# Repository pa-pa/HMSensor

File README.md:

# HMSensor

Flexible and tiny (40x20mm) Hardware Platform for 868MHz Sensors and Actors.

It comes in tow different variants:
* StepUp: For Batter or PowerSupply usage
* CR2032: For even smaller coin battery applications

Extensible with [AddOn-Boards](AddOns).

* Some (german) documentation is available at https://asksinpp.de/Projekte/psi/HMSensor
* Helper PCB for flashing: https://github.com/psi-4ward/HMSensor-FlashStation

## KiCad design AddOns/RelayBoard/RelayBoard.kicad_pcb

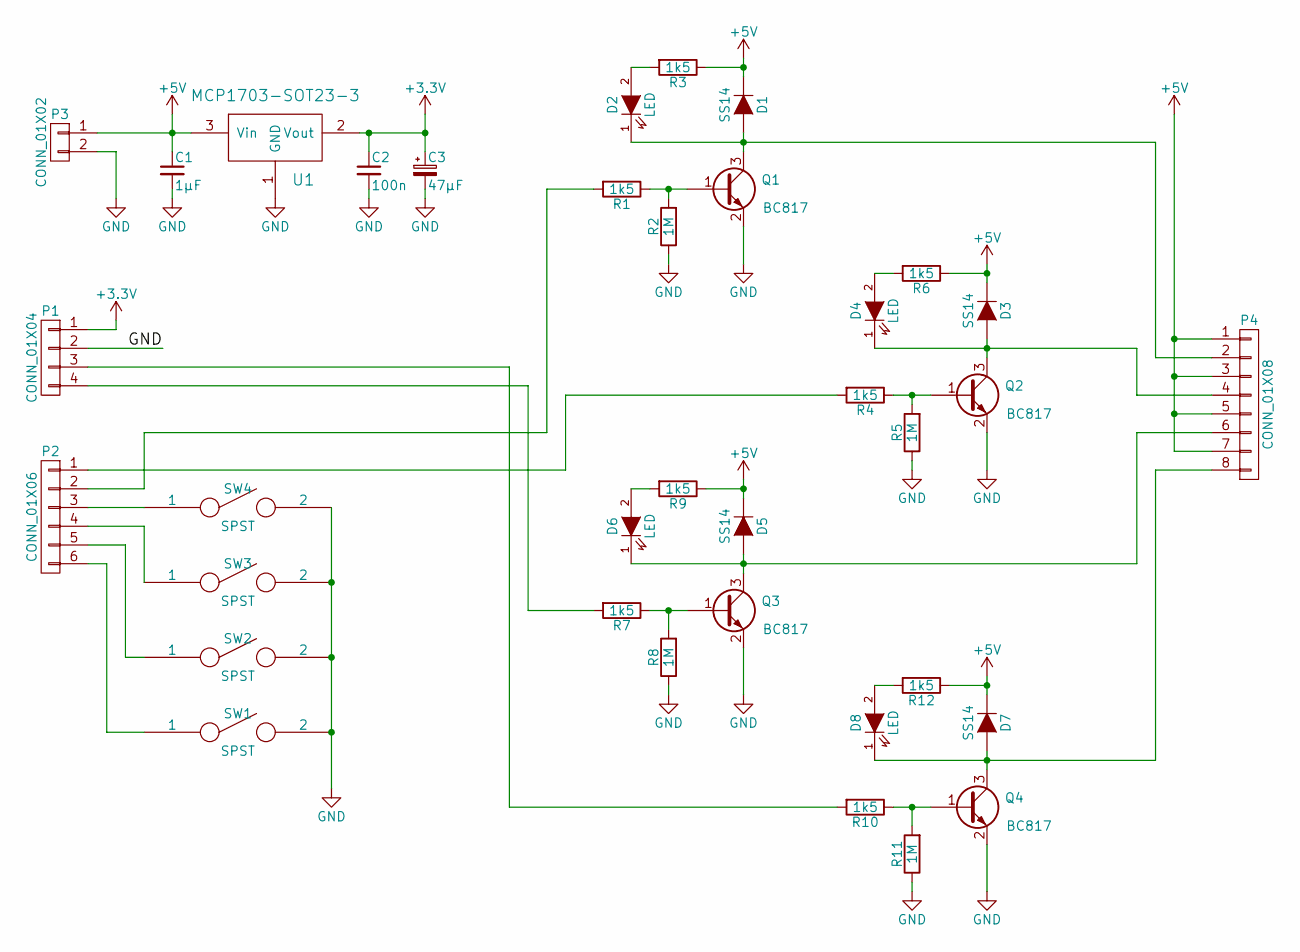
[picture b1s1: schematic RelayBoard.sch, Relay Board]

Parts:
C1: 1µF; C_0805
C2: 100n; C_0805
C3: 47µF; CP_Tantalum_Case-T_EIA-3528-12_Reflow
D1, D3, D5, D7: SS14; D_SMA
D2, D4, D6, D8: LED; LED_1206
P1: CONN_01X04; Pin_Header_Straight_1x04_Pitch2.54mm
P2: CONN_01X06; Pin_Header_Straight_1x06_Pitch2.54mm
P3: CONN_01X02; Pin_Header_Straight_1x02_Pitch2.54mm
P4: CONN_01X08; Pin_Header_Straight_1x08_Pitch2.54mm
Q1, Q2, Q3, Q4: BC817; SOT-23-3
R1, R3, R4, R6, R7, R9, R10, R12: 1k5; R_0805
R2, R5, R8, R11: 1M; R_0805
SW1, SW2, SW3, SW4: SPST; SW_SPST_FSMSM
U1: MCP1703-SOT23-3; SOT-23-3

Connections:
+3V3: C2.1, C3.1, P1.1, U1.2 (Vout)
+5V: C1.1, D1.1 (K), D3.1 (K), D5.1 (K), D7.1 (K), P3.1, P4.1, P4.3, P4.5, P4.7, R3.1, R6.1, R9.1, R12.1, U1.3 (Vin)
GND: C1.2, C2.2, C3.2, P1.2, P3.2, Q1.2 (E), Q2.2 (E), Q3.2 (E), Q4.2 (E), R2.1, R5.1, R8.1, R11.1, SW1.2, SW2.2, SW3.2, SW4.2, U1.1 (GND)
unnamed: D1.2 (A), D2.1 (K), P4.2, Q1.3 (C)
unnamed: D2.2 (A), R3.2
unnamed: D3.2 (A), D4.1 (K), P4.4, Q2.3 (C)
unnamed: D4.2 (A), R6.2
unnamed: D5.2 (A), D6.1 (K), P4.6, Q3.3 (C)
unnamed: D6.2 (A), R9.2
unnamed: D7.2 (A), D8.1 (K), P4.8, Q4.3 (C)
unnamed: D8.2 (A), R12.2
unnamed: P1.3, R10.2
unnamed: P1.4, R7.2
unnamed: P2.1, R4.2
unnamed: P2.2, R1.2
unnamed: P2.3, SW4.1
unnamed: P2.4, SW3.1
unnamed: P2.5, SW2.1
unnamed: P2.6, SW1.1
unnamed: Q1.1 (B), R1.1, R2.2
unnamed: Q2.1 (B), R4.1, R5.2
unnamed: Q3.1 (B), R7.1, R8.2
unnamed: Q4.1 (B), R10.1, R11.2

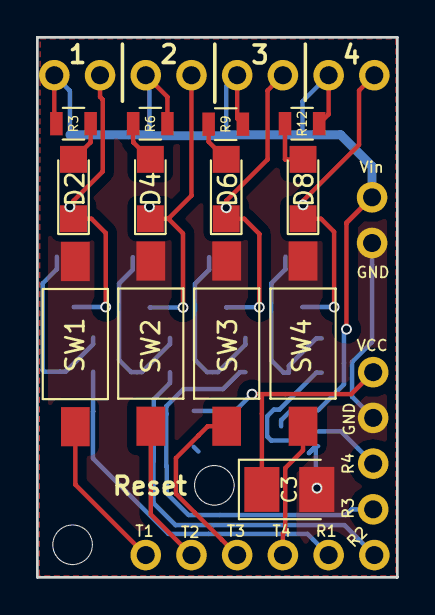
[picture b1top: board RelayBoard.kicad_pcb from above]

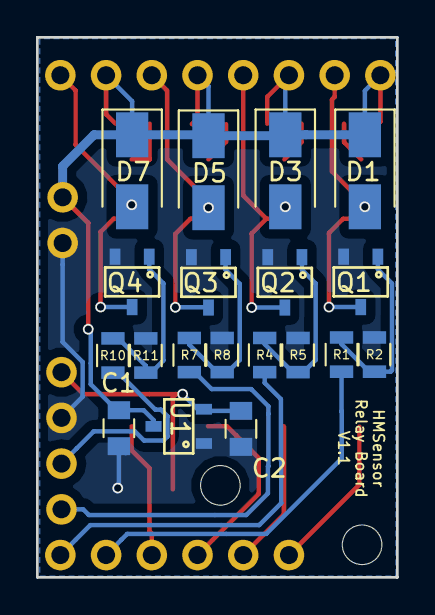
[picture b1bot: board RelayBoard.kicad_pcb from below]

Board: 2 copper layers, 20.0 x 30.0 mm, 36 parts (19 on the bottom side), 23 nets.

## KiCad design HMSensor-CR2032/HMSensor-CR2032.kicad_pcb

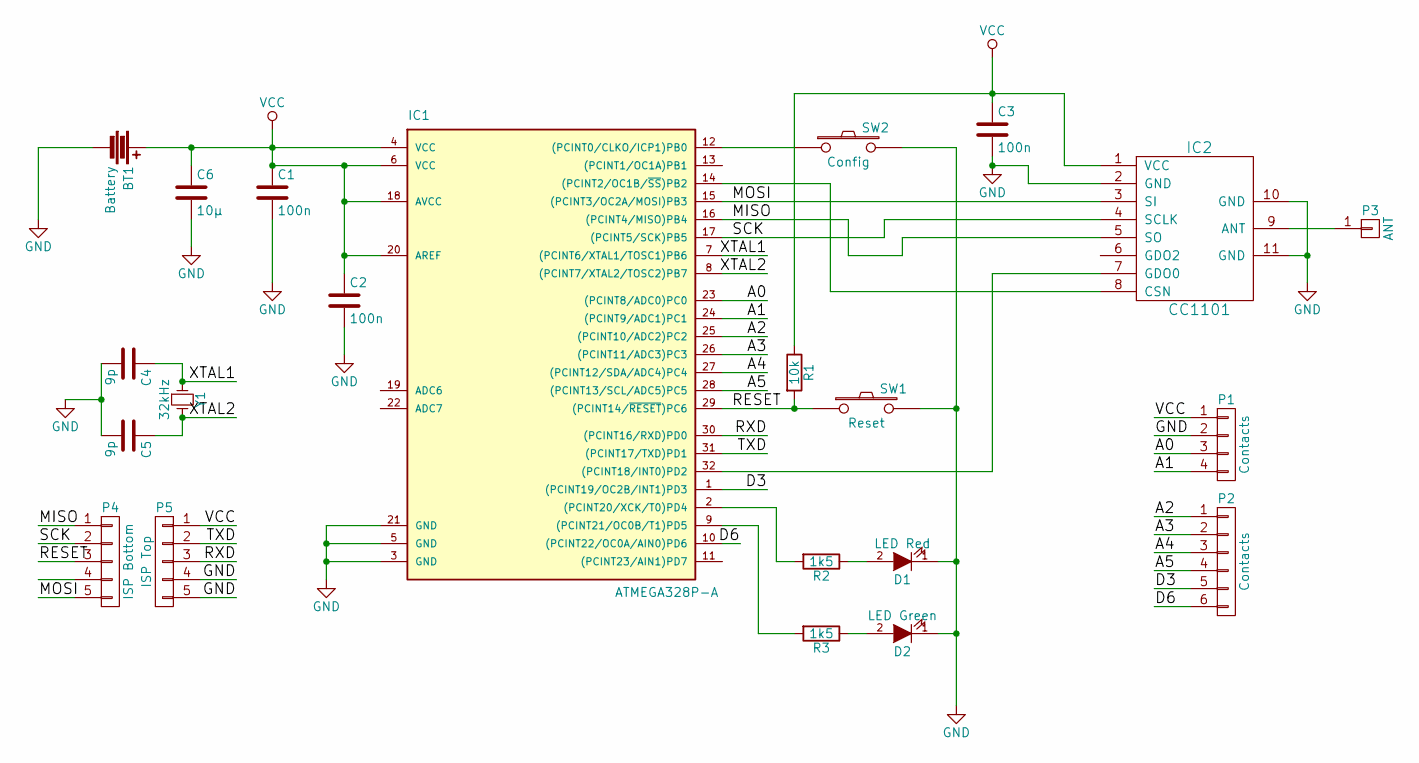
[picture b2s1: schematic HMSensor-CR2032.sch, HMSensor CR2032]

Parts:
BT1: Battery; AB2_20MM_COIN_CELL_SMD
C1, C2, C3: 100n; C_0805_HandSoldering
C4, C5: 9p; C_0805_HandSoldering
C6: 10µ; C_0805_HandSoldering
D1: LED Red; LED_1206
D2: LED Green; LED_1206
IC1: ATMEGA328P-A; TQFP-32_7x7mm_Pitch0.8mm
IC2: CC1101; CC1101_Module
P1: Contacts; Pin_Header_Straight_1x04_Pitch2.54mm
P2: Contacts; Pin_Header_Straight_1x06_Pitch2.54mm
P3: ANT; Pin_Header_Straight_1x01_Pitch2.00mm
P4: ISP Bottom; Pin_Header_Straight_1x05_Pitch2.54mm_SMD_BySide
P5: ISP Top; Pin_Header_Straight_1x05_Pitch2.54mm_SMD_BySide
R1: 10k; R_0805_HandSoldering
R2, R3: 1k5; R_0805_HandSoldering
SW1: Reset; SW_SPST_FSMSM
SW2: Config; SW_SPST_FSMSM
Y1: 32kHz; Crystal_SMD_MicroCrystal_CC7V-T1A-2pin_3.2x1.5mm_HandSolder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

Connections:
/A0: IC1.23 ((PCINT8/ADC0)PC0), P1.3
/A1: IC1.24 ((PCINT9/ADC1)PC1), P1.4
/A2: IC1.25 ((PCINT10/ADC2)PC2), P2.1
/A3: IC1.26 ((PCINT11/ADC3)PC3), P2.2
/A4: IC1.27 ((PCINT12/SDA/ADC4)PC4), P2.3
/A5: IC1.28 ((PCINT13/SCL/ADC5)PC5), P2.4
/D3: IC1.1 ((PCINT19/OC2B/INT1)PD3), P2.5
/D6: IC1.10 ((PCINT22/OC0A/AIN0)PD6), P2.6
/MISO: IC1.16 ((PCINT4/MISO)PB4), IC2.5 (SO), P4.1
/MOSI: IC1.15 ((PCINT3/OC2A/MOSI)PB3), IC2.3 (SI), P4.5
/RESET: IC1.29 ((PCINT14/~RESET~)PC6), P4.3, R1.2, SW1.1
/RXD: IC1.30 ((PCINT16/RXD)PD0), P5.3
/SCK: IC1.17 ((PCINT5/SCK)PB5), IC2.4 (SCLK), P4.2
/TXD: IC1.31 ((PCINT17/TXD)PD1), P5.2
/XTAL1: C4.1, IC1.7 ((PCINT6/XTAL1/TOSC1)PB6), Y1.1
/XTAL2: C5.1, IC1.8 ((PCINT7/XTAL2/TOSC2)PB7), Y1.2
GND: BT1.2, C1.2, C2.2, C3.2, C4.2, C5.2, C6.2, D1.1 (K), D2.1 (K), IC1.3 (GND), IC1.5 (GND), IC1.21 (GND), IC2.2 (GND), IC2.10 (GND), IC2.11 (GND), P1.2, P5.4, P5.5, SW1.2, SW2.2
unnamed: D1.2 (A), R2.1
unnamed: D2.2 (A), R3.1
unnamed: IC1.2 ((PCINT20/XCK/T0)PD4), R2.2
unnamed: IC1.9 ((PCINT21/OC0B/T1)PD5), R3.2
unnamed: IC1.12 ((PCINT0/CLKO/ICP1)PB0), SW2.1
unnamed: IC1.14 ((PCINT2/OC1B/~SS~)PB2), IC2.8 (CSN)
unnamed: IC1.32 ((PCINT18/INT0)PD2), IC2.7 (GDO0)
unnamed: IC2.9 (ANT), P3.1
VCC: BT1.1, C1.1, C2.1, C3.1, C6.1, IC1.4 (VCC), IC1.6 (VCC), IC1.18 (AVCC), IC1.20 (AREF), IC2.1 (VCC), P1.1, P5.1, R1.1

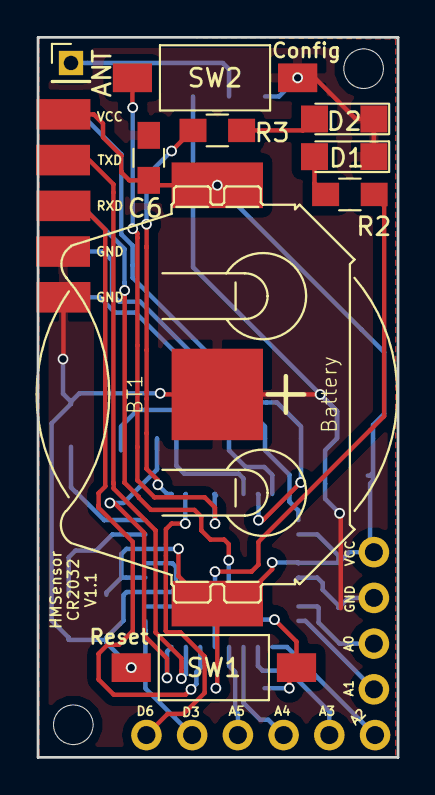
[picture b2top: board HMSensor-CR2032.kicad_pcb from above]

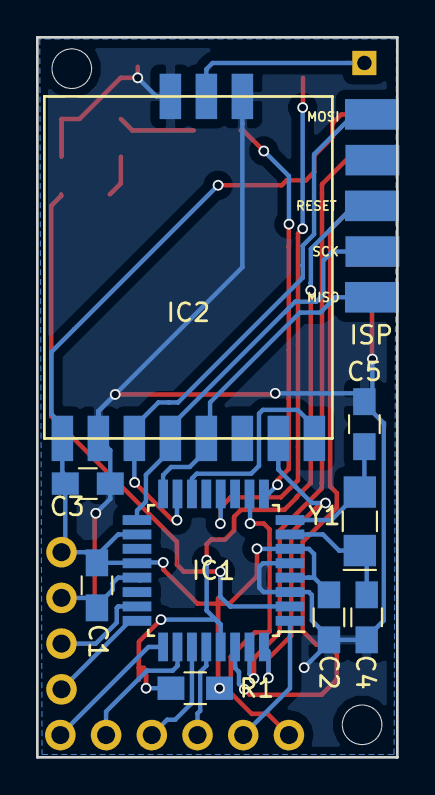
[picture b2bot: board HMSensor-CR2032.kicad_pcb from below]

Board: 2 copper layers, 20.0 x 40.0 mm, 22 parts (10 on the bottom side), 26 nets.

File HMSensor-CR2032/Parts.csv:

"Id";"Designator";"Package";"Quantity";"Designation";"Supplier and ref";
1;"P4";"Pin_Header_Straight_1x05_Pitch2.54mm_SMD_BySide";1;"ISP Bottom";;;
2;"P5";"Pin_Header_Straight_1x05_Pitch2.54mm_SMD_BySide";1;"ISP Top";;;
3;"IC1";"TQFP-32_7x7mm_Pitch0.8mm";1;"ATMEGA328P-A";;;
4;"P1";"Pin_Header_Straight_1x04_Pitch2.54mm";1;"Contacts";;;
5;"P2";"Pin_Header_Straight_1x06_Pitch2.54mm";1;"Contacts";;;
6;"BT1";"AB2_20MM_COIN_CELL_SMD";1;"Battery";;;
7;"IC2";"CC1101_Module";1;"CC1101";;;
8;"SW1";"SW_SPST_FSMSM";1;"Reset";;;
9;"SW2";"SW_SPST_FSMSM";1;"Config";;;
10;"C1,C2,C3";"C_0805_HandSoldering";3;"100n";;;
11;"D1";"LED_1206";1;"LED Red";;;
12;"D2";"LED_1206";1;"LED Green";;;
13;"R1";"R_0805_HandSoldering";1;"10k";;;
14;"R2,R3";"R_0805_HandSoldering";2;"1k5";;;
15;"C4,C5";"C_0805_HandSoldering";2;"9p";;;
16;"Y1";"Crystal_SMD_MicroCrystal_CC7V-T1A-2pin_3.2x1.5mm_HandSoldering";1;"32kHz";;;
17;"REF**,REF**";"MountingHole_2.2mm_M2";2;"MountingHole_2.2mm_M2";;;
18;"P3";"Pin_Header_Straight_1x01_Pitch2.00mm";1;"ANT";;;
19;"C6";"C_0805_HandSoldering";1;"10µ";;;

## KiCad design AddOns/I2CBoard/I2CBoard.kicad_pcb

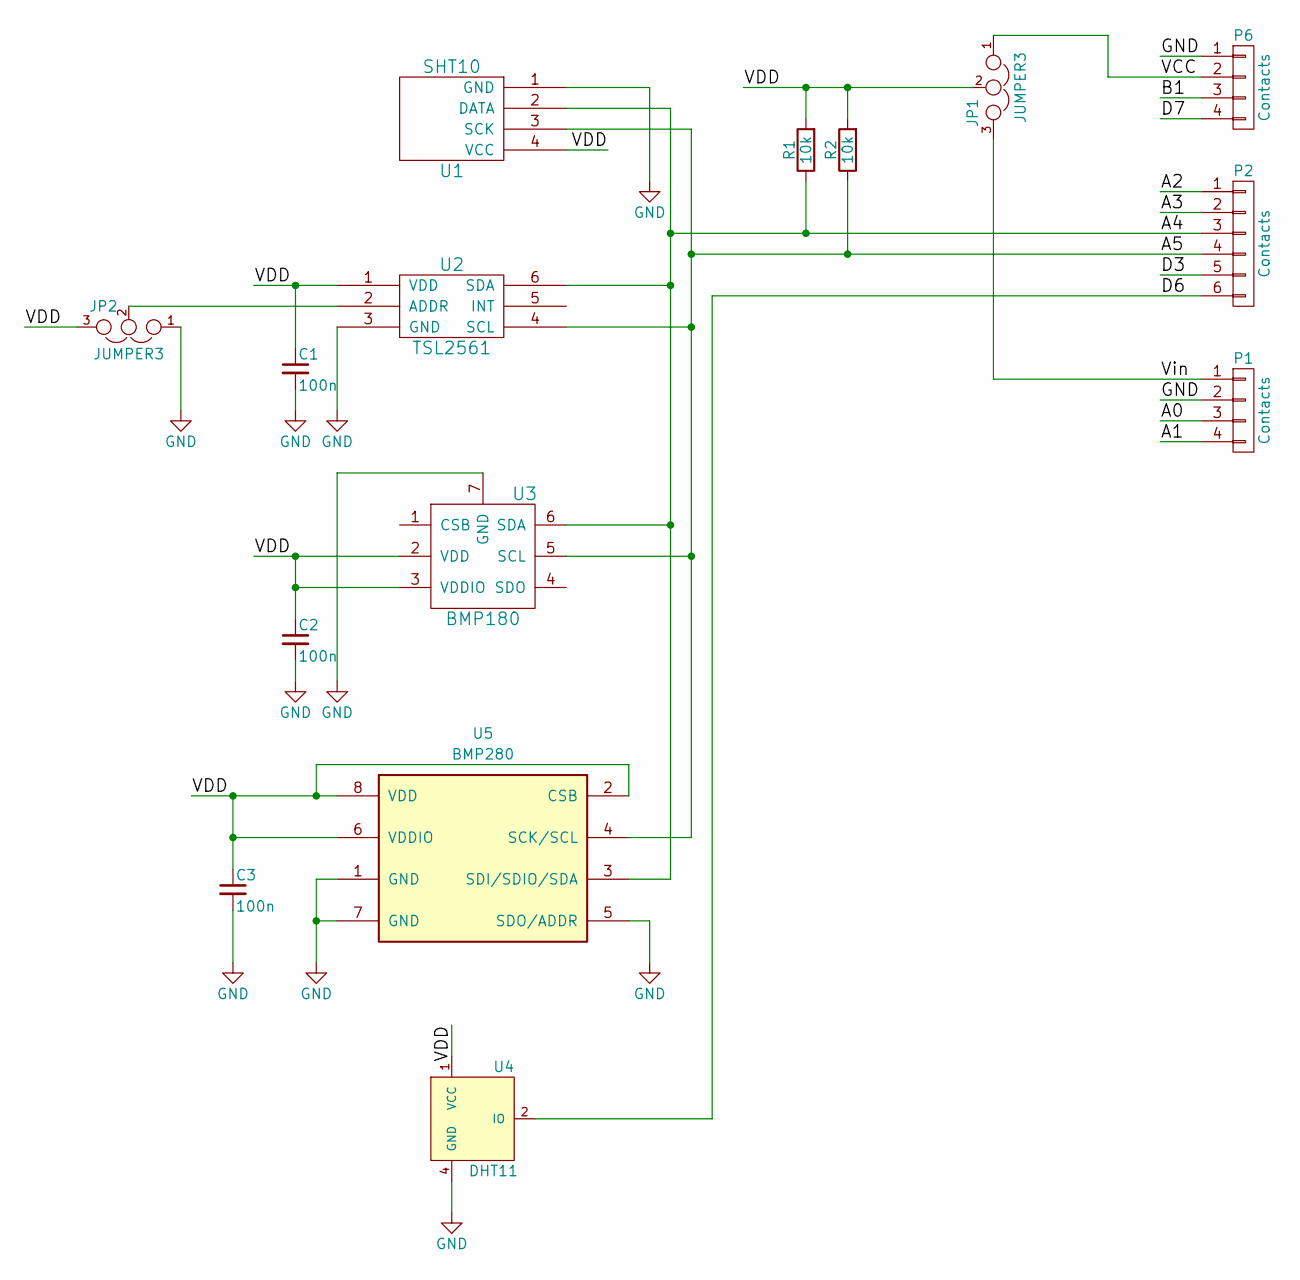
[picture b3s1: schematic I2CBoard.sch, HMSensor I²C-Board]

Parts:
C1, C2, C3: 100n; C_0805_HandSoldering
JP1, JP2: JUMPER3; GS3
P1, P6: Contacts; Pin_Header_Straight_1x04_Pitch2.54mm
P2: Contacts; Pin_Header_Straight_1x06_Pitch2.54mm
R1, R2: 10k; R_0805_HandSoldering
U1: SHT10; SHT1x
U2: TSL2561; TSL256x
U3: BMP180; LGA_BMP180
U4: DHT11; Pin_Header_Straight_1x04_Pitch2.00mm
U5: BMP280; BOSCH_BMP280; MPN BMP280

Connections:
/A0: P1.3
/A1: P1.4
/A2: P2.1
/A3: P2.2
/A4: P2.3, R1.1, U1.2 (DATA), U2.6 (SDA), U3.6 (SDA), U5.3 (SDI/SDIO/SDA)
/A5: P2.4, R2.1, U1.3 (SCK), U2.4 (SCL), U3.5 (SCL), U5.4 (SCK/SCL)
/B1: P6.3
/D3: P2.5
/D6: P2.6, U4.2 (IO)
/D7: P6.4
/VCC: JP1.1, P6.2
/VDD: C1.1, C2.1, C3.1, JP1.2, JP2.3, R1.2, R2.2, U1.4 (VCC), U2.1 (VDD), U3.2 (VDD), U3.3 (VDDIO), U4.1 (VCC), U5.2 (CSB), U5.6 (VDDIO), U5.8 (VDD)
/Vin: JP1.3, P1.1
GND: C1.2, C2.2, C3.2, JP2.1, P1.2, P6.1, U1.1 (GND), U2.3 (GND), U3.7 (GND), U4.4 (GND), U5.1 (GND), U5.5 (SDO/ADDR), U5.7 (GND)
unnamed: JP2.2, U2.2 (ADDR)

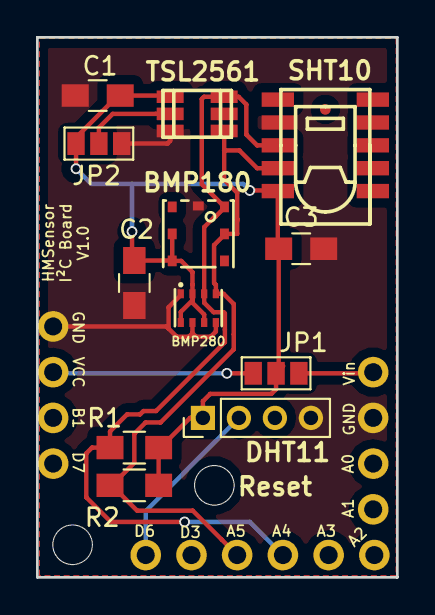
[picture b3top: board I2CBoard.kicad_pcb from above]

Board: 2 copper layers, 20.0 x 30.0 mm, 15 parts (0 on the bottom side), 8 nets.

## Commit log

2017-07-06 panel added
2017-07-07 try to fix panel problem with 18650 board
2017-08-08 relay board added
2017-08-10 panel updated with relay addon
2017-08-18 fix layout problems
2017-08-18 18650 gerber fixed
2017-09-05 I²C V1.1 Relay V1.1
2017-09-15 V1.1 Update
2018-02-17 V1.1 Panel
